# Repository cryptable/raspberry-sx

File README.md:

# raspberry-sx

Cyberdesck based on old [Commodore 64 SX](https://en.wikipedia.org/wiki/Commodore_SX-64). 

It uses a Raspberry Pi 4 with Wifi and 8Gb memory. There is an SSD attached to it using one of the USB 3.0 ports. The other USB 3.0 is used to attach a USB hub. On the USB 2.0 port is a keyboard attached and the other USB 2.0 port is used for the touch screen. It is powered by a powerbank, which is charged using a power supply. There is much place left in the cyberdeck to add other measuring instruments or a Pi modules cluster. 

It is open-source and you can adapt the design as you wish as long as you send me a pictures of your usage with a explanation of usage. 

And when we meet in person, you can also buy me a beer. 

More information is found under the [docs](./docs/cyberdeck-body.md).

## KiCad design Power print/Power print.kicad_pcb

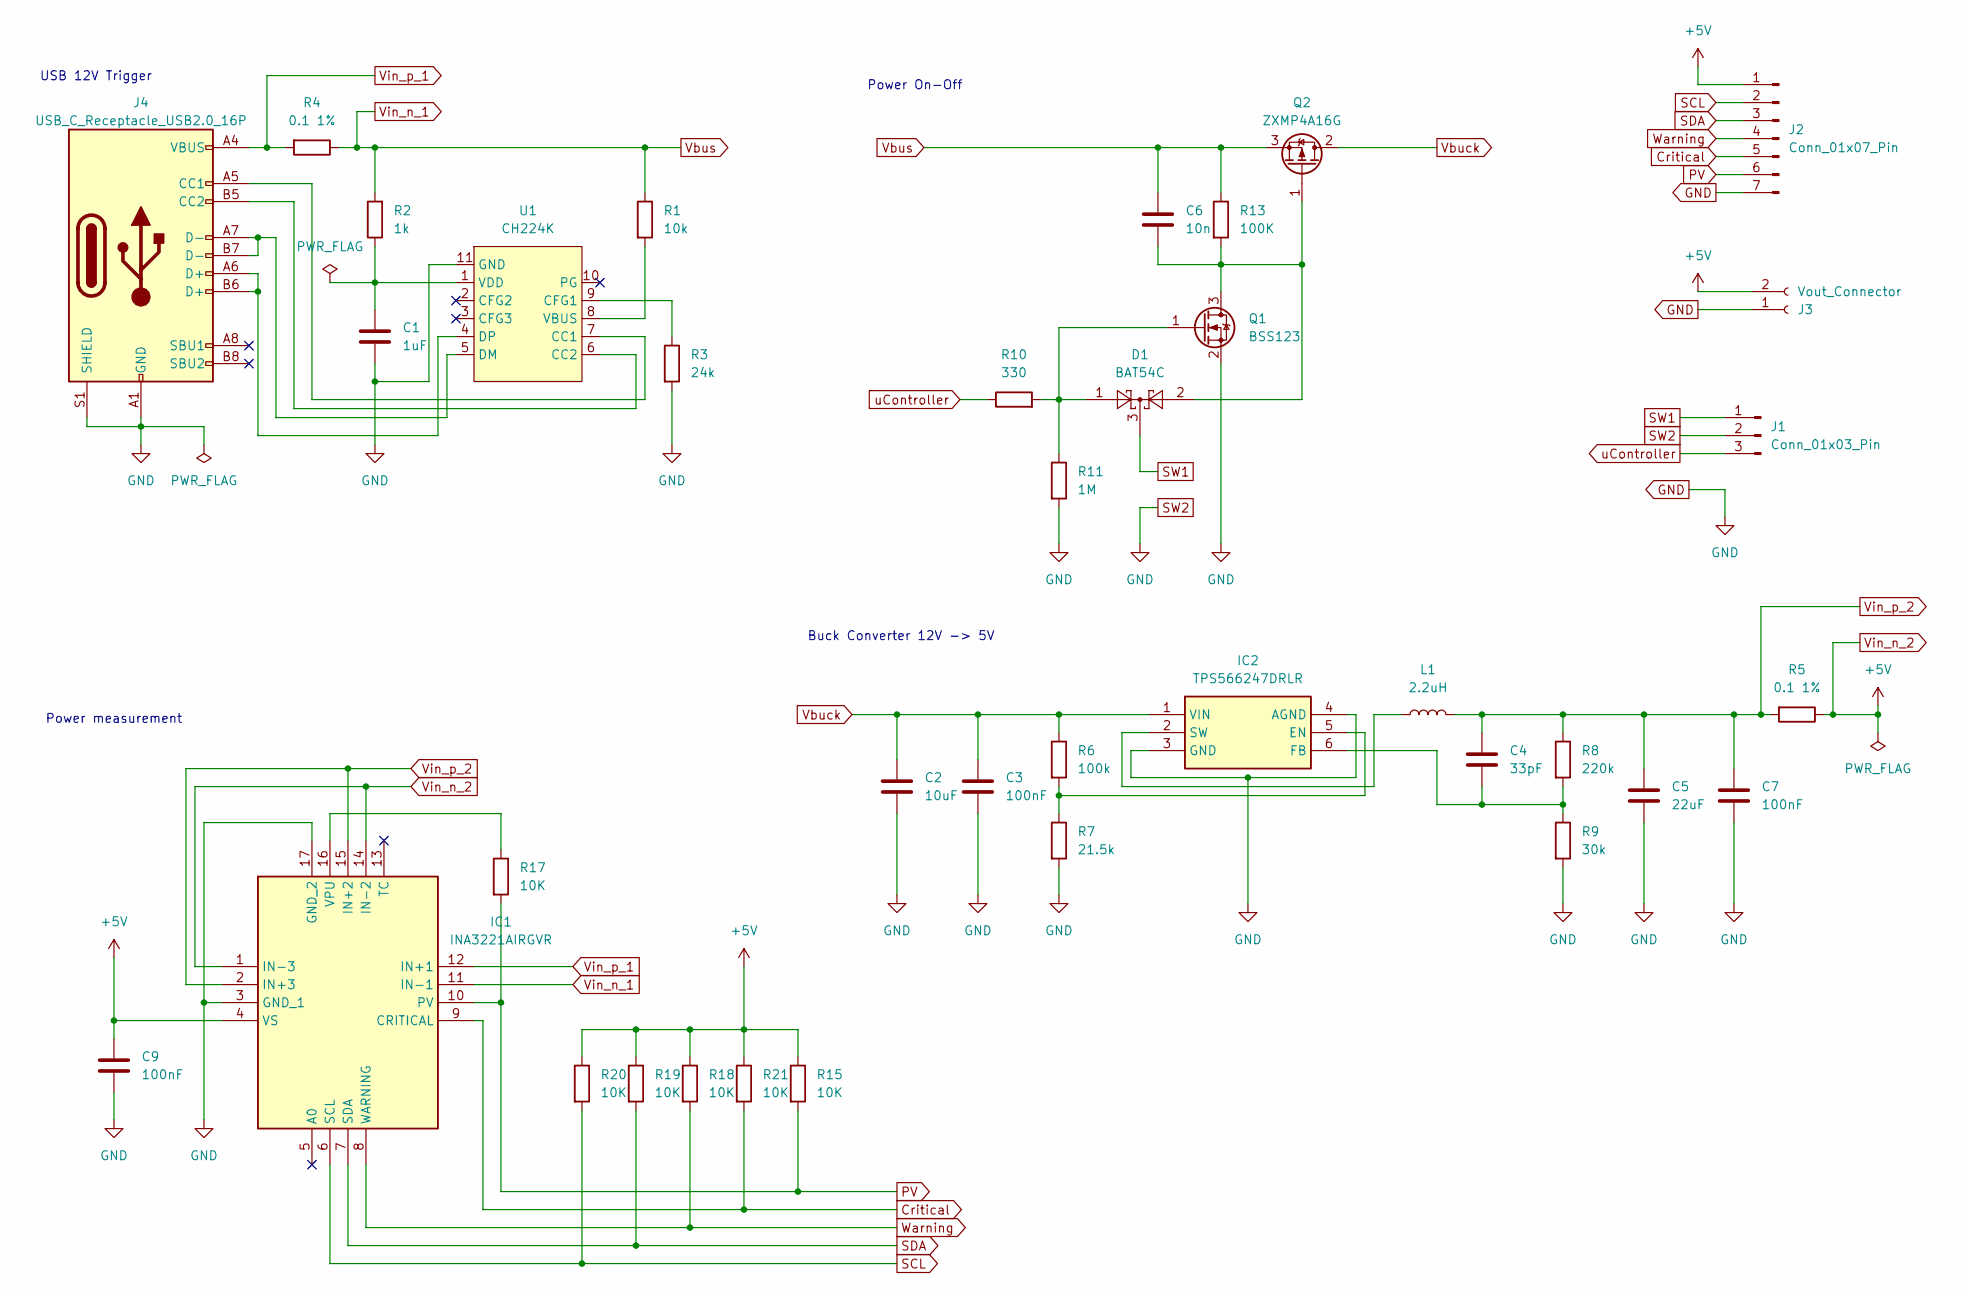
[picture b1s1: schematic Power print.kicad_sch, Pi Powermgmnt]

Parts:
C1: 1uF; C_1206_3216Metric_Pad1.33x1.80mm_HandSolder; LCSC C1848
C2: 10uF; C_1206_3216Metric_Pad1.33x1.80mm_HandSolder; LCSC C1849
C3, C7, C9: 100nF; C_1206_3216Metric_Pad1.33x1.80mm_HandSolder; LCSC C1945
C4: 33pF; C_1206_3216Metric_Pad1.33x1.80mm_HandSolder; LCSC C1906
C5: 22uF; C_1206_3216Metric_Pad1.33x1.80mm_HandSolder; LCSC C12891
C6: 10n; C_0805_2012Metric_Pad1.18x1.45mm_HandSolder; LCSC C1710
D1: BAT54C; SOT-23; LCSC C916424
IC1: INA3221AIRGVR; QFN-16_L4.0-W4.0-P0.65-TL-EP2.2; Manufacturer_Part_Number INA3221AIRGVR; LCSC C181255
IC2: TPS566247DRLR; SOT-563; Manufacturer_Part_Number TPS566247DRLR; LCSC C5219274
J1: Conn_01x03_Pin; PinHeader_1x03_P1.00mm_Vertical
J2: Conn_01x07_Pin; PinHeader_1x07_P1.00mm_Vertical
J3: Vout_Connector; CONN-TH_P5.00_KF301-5.0-2P; LCSC C474881
J4: USB_C_Receptacle_USB2.0_16P; USB_C_Receptacle_GCT_USB4105-xx-A_16P_TopMnt_Horizontal; LCSC C2965608
L1: 2.2uH; IND-SMD_L7.2-W6.6_GPSR07X0; LCSC C5189746
Q1: BSS123; SOT-23; LCSC C7420338
Q2: ZXMP4A16G; SOT-223-3_TabPin2; LCSC C141324
R1: 10k; R_1206_3216Metric_Pad1.30x1.75mm_HandSolder; LCSC C326700
R2: 1k; R_1206_3216Metric_Pad1.30x1.75mm_HandSolder; LCSC C2759097
R3: 24k; R_1206_3216Metric_Pad1.30x1.75mm_HandSolder; LCSC C2759176
R4, R5: 0.1 1%; R_2512_6332Metric_Pad1.40x3.35mm_HandSolder; LCSC C7419997
R6: 100k; R_1206_3216Metric_Pad1.30x1.75mm_HandSolder; LCSC C606185
R7: 21.5k; R_1206_3216Metric_Pad1.30x1.75mm_HandSolder; LCSC C311938
R8: 220k; R_1210_3225Metric_Pad1.30x2.65mm_HandSolder; LCSC C606197
R9: 30k; R_1206_3216Metric_Pad1.30x1.75mm_HandSolder; LCSC C3013378
R10: 330; R_1206_3216Metric_Pad1.30x1.75mm_HandSolder; LCSC C3013376
R11: 1M; R_1210_3225Metric_Pad1.30x2.65mm_HandSolder; LCSC C470029
R13: 100K; R_1206_3216Metric_Pad1.30x1.75mm_HandSolder; LCSC C606185
R15, R17, R18, R19, R20, R21: 10K; R_1206_3216Metric_Pad1.30x1.75mm_HandSolder; LCSC C326700
U1: CH224K; ESSOP-10_L4.9-W3.9-P1.0-LS6.0-TL-EP; LCSC C970725

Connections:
Critical: IC1.9 (CRITICAL), J2.5, R21.2
GND: C1.2, C2.2, C3.2, C5.2, C7.2, C9.2, IC1.3 (GND_1), IC1.17 (GND_2), IC2.3 (GND), IC2.4 (AGND), J1.2, J2.7, J3.1, J4.A1 (GND), J4.A12 (GND), J4.B1 (GND), J4.B12 (GND), J4.S1 (SHIELD), Q1.2 (S), R3.2, R7.2, R9.2, R11.2, U1.11 (GND)
unnamed: IC1.16 (VPU), R17.1
unnamed: IC2.5 (EN), R6.2, R7.1
unnamed: C4.2, IC2.6 (FB), R8.2, R9.1
unnamed: IC2.2 (SW), L1.1
unnamed: J4.A5 (CC1), U1.7 (CC1)
unnamed: J4.B5 (CC2), U1.6 (CC2)
unnamed: C6.2, D1.2, Q1.3 (D), Q2.1 (G), R13.2
unnamed: D1.1, Q1.1 (G), R10.2, R11.1
unnamed: R3.1, U1.9 (CFG1)
unnamed: J4.A7 (D-), J4.B7 (D-), U1.5 (DM)
unnamed: J4.A6 (D+), J4.B6 (D+), U1.4 (DP)
unnamed: R1.2, U1.8 (VBUS)
unnamed: C1.1, R2.1, U1.1 (VDD)
PV: IC1.10 (PV), J2.6, R15.2, R17.2
SCL: IC1.6 (SCL), J2.2, R20.2
SDA: IC1.7 (SDA), J2.3, R19.2
SW1: D1.3, J1.1
Vbuck: C2.1, C3.1, IC2.1 (VIN), Q2.2 (D), R6.1
Vbus: C6.1, IC1.11 (IN-1), Q2.3 (S), R1.1, R2.2, R4.1, R13.1
Vin_n_2: C9.1, IC1.1 (IN-3), IC1.4 (VS), IC1.14 (IN-2), J2.1, J3.2, R5.1, R15.1, R18.1, R19.1, R20.1, R21.1
Vin_p_1: IC1.12 (IN+1), J4.A4 (VBUS), J4.A9 (VBUS), J4.B4 (VBUS), J4.B9 (VBUS), R4.2
Vin_p_2: C4.1, C5.1, C7.1, IC1.2 (IN+3), IC1.15 (IN+2), L1.2, R5.2, R8.1
Warning: IC1.8 (WARNING), J2.4, R18.2
uController: J1.3, R10.1

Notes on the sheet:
Power On-Off
USB 12V Trigger
Power measurement
Buck Converter 12V -> 5V

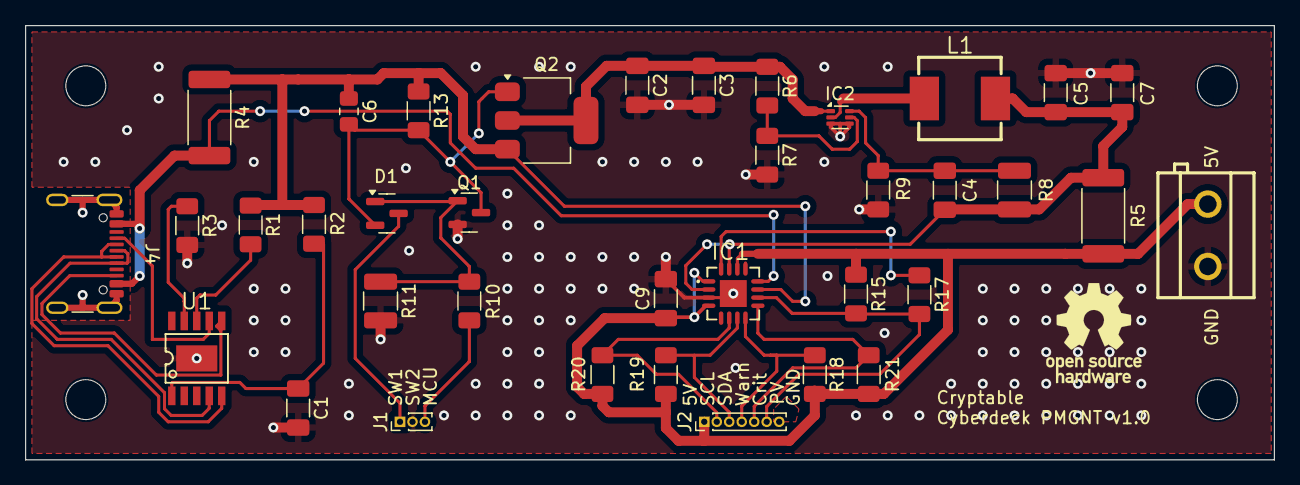
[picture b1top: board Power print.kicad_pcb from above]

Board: 2 copper layers, 100.1 x 34.8 mm, 37 parts (0 on the bottom side), 26 nets.

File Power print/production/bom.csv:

Designator,Footprint,Quantity,Value,LCSC Part #
C1,1206,1,1uF,C1848
C2,1206,1,10uF,C1849
"C3, C7, C9",1206,3,100nF, C1945
C4,1206,1,33pF,C1906
C5,1206,1,22uF, C12891
C6,0805,1,10n, C1710
D1,SOT-23,1,BAT54C,C916424
IC1,QFN-16_L4.0-W4.0-P0.65-TL-EP2.2,1,INA3221AIRGVR,C181255
IC2,SOT-563,1,TPS566247DRLR,C5219274
J1,PinHeader_1x03_P1.00mm_Vertical,1,Conn_01x03_Pin,
J2,PinHeader_1x07_P1.00mm_Vertical,1,Conn_01x07_Pin,
J3,CONN-TH_P5.00_KF301-5.0-2P,1,Vout_Connector,C474881
J4,USB_C_Receptacle_GCT_USB4105-xx-A_16P_TopMnt_Horizontal,1,USB_C_Receptacle_USB2.0_16P,C2965608
L1,IND-SMD_L7.2-W6.6_GPSR07X0,1,2.2uH,C5189746
Q1,SOT-23,1,BSS123,C7420338
Q2,SOT-223-3_TabPin2,1,ZXMP4A16G, C141324
"R1, R15, R17, R18, R19, R20, R21",1206,7,10k,C326700
R10,1206,1,330,C3013376
R11,1210,1,1M,C470029
"R13, R6",1206,2,100K,C606185
R2,1206,1,1k,C2759097
R3,1206,1,24k,C2759176
"R4, R5",2512,2,0.1 1%,C7419997
R7,1206,1,21.5k,C311938
R8,1210,1,220k,C606197
R9,1206,1,30k,C3013378
U1,ESSOP-10_L4.9-W3.9-P1.0-LS6.0-TL-EP,1,CH224K,C970725

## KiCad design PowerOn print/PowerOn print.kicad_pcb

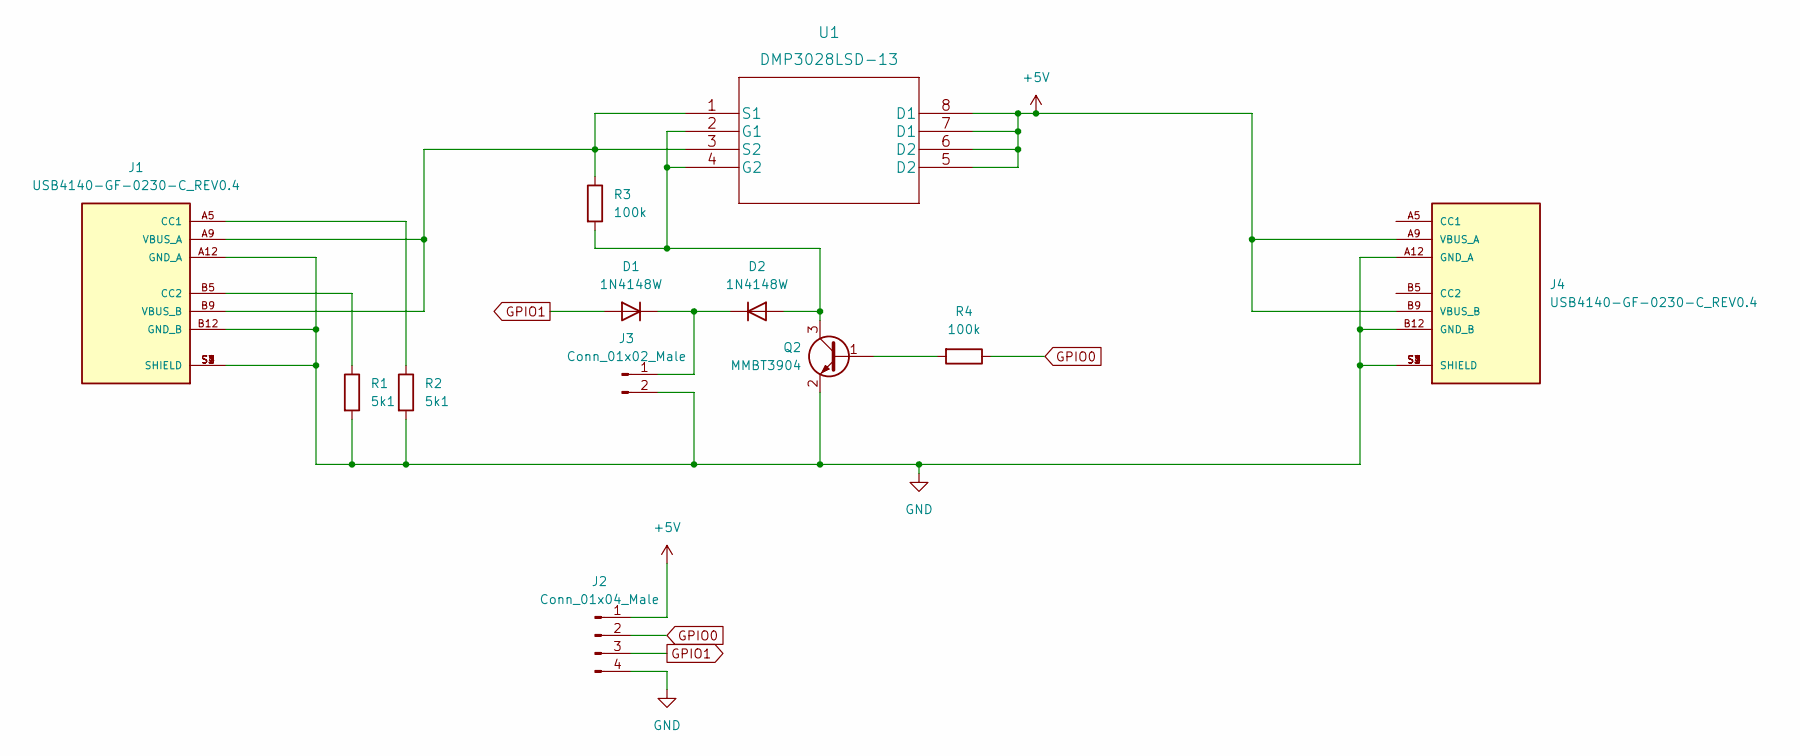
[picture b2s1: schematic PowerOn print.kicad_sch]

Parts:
D1, D2: 1N4148W; D_SOD-123
J1, J4: USB4140-GF-0230-C_REV0.4; GCT_USB4140-GF-0230-C_REV0.4; PARTREV 0.4
J2: Conn_01x04_Male; PinHeader_1x04_P2.54mm_Vertical
J3: Conn_01x02_Male; PinHeader_1x02_P2.54mm_Vertical
Q2: MMBT3904; SOT-23
R1, R2: 5k1; R_0805_2012Metric
R3, R4: 100k; R_0805_2012Metric
U1: DMP3028LSD-13

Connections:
+5V: J2.1, J4.A9 (VBUS_A), J4.B9 (VBUS_B), U1.5 (D2), U1.6 (D2), U1.7 (D1), U1.8 (D1)
GND: J1.A12 (GND_A), J1.B12 (GND_B), J1.S1 (SHIELD), J1.S2 (SHIELD), J1.S3 (SHIELD), J1.S4 (SHIELD), J2.4, J3.2, J4.A12 (GND_A), J4.B12 (GND_B), J4.S1 (SHIELD), J4.S2 (SHIELD), J4.S3 (SHIELD), J4.S4 (SHIELD), Q2.2 (E), R1.2, R2.2
GPIO0: J2.2, R4.1
GPIO1: D1.2 (A), J2.3
unnamed: D1.1 (K), D2.1 (K), J3.1
unnamed: D2.2 (A), Q2.3 (C), R3.2, U1.2 (G1), U1.4 (G2)
unnamed: J1.A5 (CC1), R2.1
unnamed: J1.A9 (VBUS_A), J1.B9 (VBUS_B), R3.1, U1.1 (S1), U1.3 (S2)
unnamed: J1.B5 (CC2), R1.1
unnamed: Q2.1 (B), R4.2

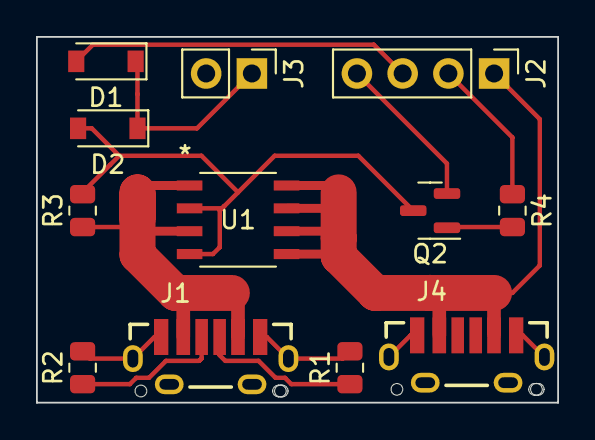
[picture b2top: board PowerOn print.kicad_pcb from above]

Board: 2 copper layers, 29.0 x 20.3 mm, 12 parts (0 on the bottom side), 10 nets.

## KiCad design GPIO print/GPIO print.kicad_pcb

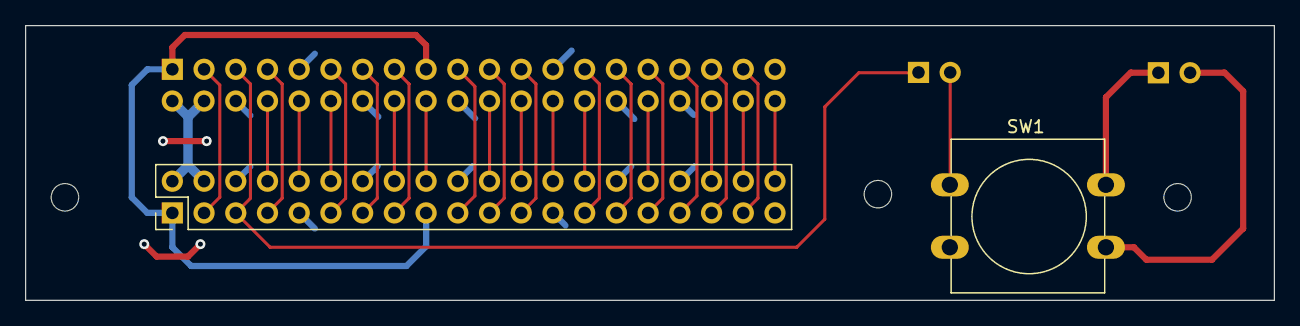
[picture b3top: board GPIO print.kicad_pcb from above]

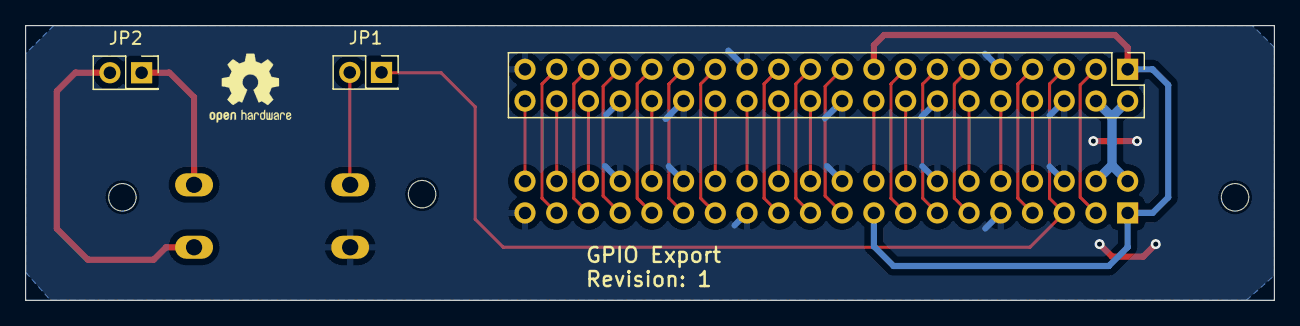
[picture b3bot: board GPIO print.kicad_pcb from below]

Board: 2 copper layers, 100.0 x 22.0 mm, 5 parts (3 on the bottom side), 34 nets.

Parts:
J1: Raspberry Out; PinHeader_2x20_P2.54mm_Vertical
J2: Raspberry In; PinHeader_2x20_P2.54mm_Vertical
JP1: Power Option; PinSocket_2x01_P2.54mm_Vertical
JP2: Other Option; PinSocket_2x01_P2.54mm_Vertical
SW1: Power Switch; SW_PUSH-12mm

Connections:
/3V3: J1.1, J1.17, J2.1, J2.17
/5V: J1.2, J1.4, J2.2, J2.4
/GPIO2: J1.3, J2.3
/GPIO4: J1.7, J2.7
/GPIO5: J1.29, J2.29
/GPIO6: J1.31, J2.31
/GPIO7: J1.26, J2.26
/GPIO8: J1.24, J2.24
/GPIO9: J1.21, J2.21
/GPIO10: J1.19, J2.19
/GPIO11: J1.23, J2.23
/GPIO12: J1.32, J2.32
/GPIO13: J1.33, J2.33
/GPIO14: J1.8, J2.8
/GPIO15: J1.10, J2.10
/GPIO16: J1.36, J2.36
/GPIO17: J1.11, J2.11
/GPIO18: J1.12, J2.12
/GPIO19: J1.35, J2.35
/GPIO20: J1.38, J2.38
/GPIO21: J1.40, J2.40
/GPIO22: J1.15, J2.15
/GPIO23: J1.16, J2.16
/GPIO24: J1.18, J2.18
/GPIO25: J1.22, J2.22
/GPIO26: J1.37, J2.37
/GPIO27: J1.13, J2.13
/ID_SC: J1.28, J2.28
/ID_SD: J1.27, J2.27
GND: J1.6, J1.9, J1.14, J1.20, J1.25, J1.30, J1.34, J1.39, J2.6, J2.9, J2.14, J2.20, J2.25, J2.30, J2.34, J2.39, SW1.2
GPIO3: J1.5, J2.5, JP1.1 (A)
unnamed: JP1.2 (B), SW1.1
unnamed: JP2.1 (A), SW1.3
unnamed: JP2.2 (B), SW1.4

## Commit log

2022-04-03 Initial Cyberdesk
2022-04-04 Change height to 120 mm
2022-04-05 Screen holders
2022-04-05 Screw holes for frontplane
2022-04-05 Documentation On/Off
2022-04-06 Moved keyboard plane 3 mm
2022-04-06 Moved the keyboard to fit the JJ50 and keys
2022-04-06 USBHolder
2022-04-06 Chamfer the panel
2022-04-06 Print keyboard
2022-04-07 Fix Keyboard tubes, which were floating
2022-04-08 Some small changes
2022-04-08 Spacebar support
2022-04-22 Keyboard text
2022-04-22 Keyboard text, added pictures
2022-04-22 typo
2022-07-10 Adjust panels
2022-07-10 New USB carrier
2022-07-11 sdd case
2022-07-11 Added Logo and keyboard cable entry
2022-07-13 add print for switch and GPIO
2022-07-13 Add rubber sealing for screen
2022-07-17 Added lock holes to main body
2022-07-18 Lockholes for bottom
2022-07-19 Front standoffs
2022-07-19 Started sketch back panel
2022-07-21 back panel
2022-07-21 back panel chmfer and fillet
2022-07-21 Lock misplacement
2022-07-28 Bigger keyboard cavety
2022-07-28 Fixed bug in chamfer for backplane
2022-07-28 Backpanel screws of ventilator
2022-07-28 Backpanel move keystone RJ45 up (collided with battery-pack)
2022-08-08 Higher network connector to prevent collission with battery pack
2022-08-08 Sealings added
2023-01-11 Strengthening Pi standoffs
2023-01-12 Adjust Pi standoff for case
2023-01-12 Tiny display
2023-01-26 Power Management module
2023-01-28 Redesign Poweron system
2023-01-28 PCB-Poweron-print-only
2023-01-29 Poweron print adapted
2023-08-11 More explanation to add it into hackaday project
2024-11-04 New power print
2024-11-04 Push button circuit
2024-11-04 Updated PowerOn print
2024-11-13 Power print resistor added
2024-11-13 Schematics power mgmnt Pi
2024-11-13 Added title for power measurement
2024-11-15 Power print schematics
2024-11-17 PCB design
2024-11-18 Rotated power connector
2024-11-28 Add display informatie
2025-04-13 update schema
